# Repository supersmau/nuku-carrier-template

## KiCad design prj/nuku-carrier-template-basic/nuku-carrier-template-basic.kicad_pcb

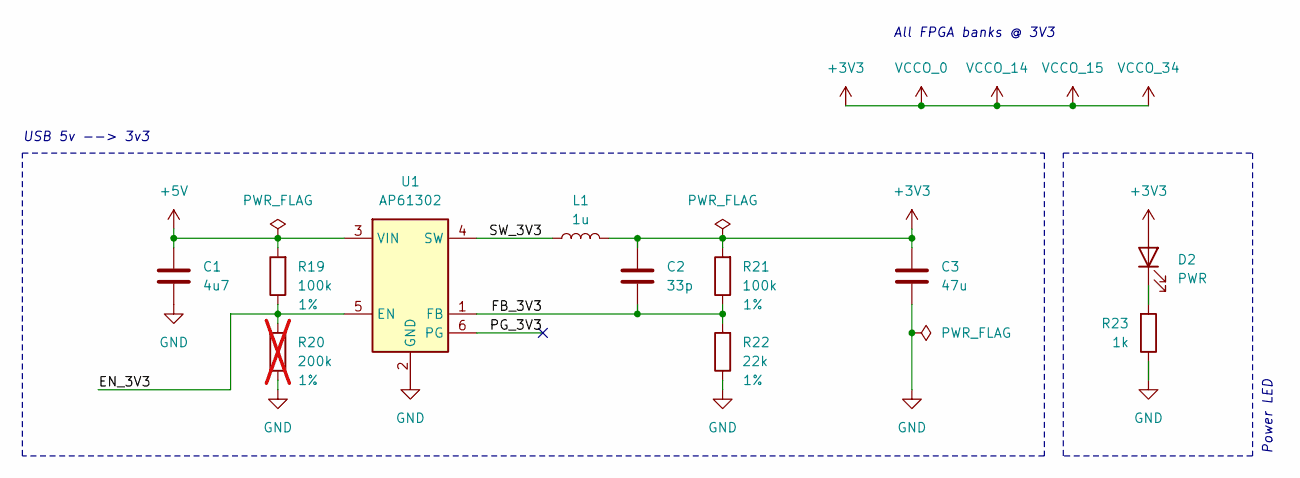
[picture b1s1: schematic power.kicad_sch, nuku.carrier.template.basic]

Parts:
C1: 4u7; C_0603_1608Metric; LCSC C19666
C2: 33p; C_0402_1005Metric; LCSC C1562
C3: 47u; C_0805_2012Metric; LCSC C16780
D2: PWR; LED_0805_2012Metric; LCSC C2297
L1: 1u; L_Changjiang_FNR252010S; Mfr. Part FTC252010S1R0MBCA; LCSC C5832356
R19, R21: 100k; R_0402_1005Metric; Tolerance 1%; LCSC C25741
R20: 200k; R_0402_1005Metric; Tolerance 1%; LCSC C25764; not fitted
R22: 22k; R_0402_1005Metric; Tolerance 1%; LCSC C25768
R23: 1k; R_0402_1005Metric; LCSC C11702
U1: AP61302; SOT-563; LCSC C3193204

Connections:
+3V3: C2.1, C3.1, D2.2 (A), L1.2, R21.2; also elsewhere on the board
+5V: C1.1, R19.2, U1.3 (VIN); also elsewhere on the board
/power/EN_3V3: R19.1, R20.2, U1.5 (EN)
/power/FB_3V3: C2.2, R21.1, R22.2, U1.1 (FB)
/power/PG_3V3: U1.6 (PG)
/power/SW_3V3: L1.1, U1.4 (SW)
GND: C1.2, C3.2, R20.1, R22.1, R23.1, U1.2 (GND); also elsewhere on the board
unnamed: D2.1 (K), R23.2

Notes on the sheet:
All FPGA banks @ 3V3
USB 5v --> 3v3
Power LED

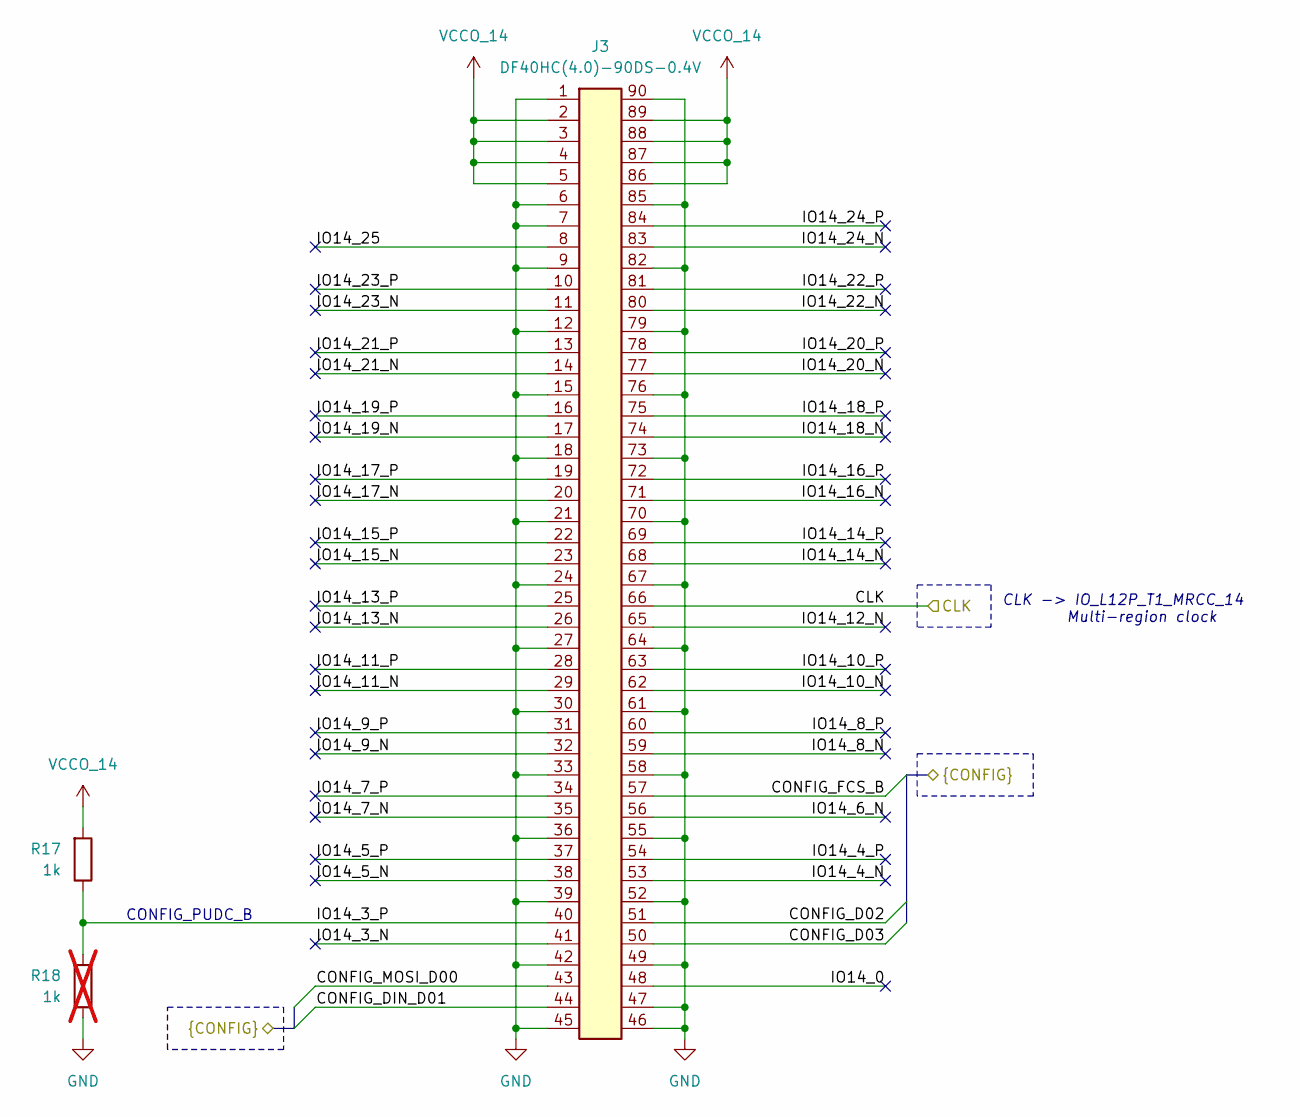
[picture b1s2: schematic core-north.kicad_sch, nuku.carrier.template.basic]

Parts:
J3: DF40HC(4.0)-90DS-0.4V; DF40C-90DS-0.4V; LCSC C2911197
R17: 1k; R_0402_1005Metric; LCSC C11702
R18: 1k; R_0402_1005Metric; LCSC C11702; not fitted

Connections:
+3V3: J3.2, J3.3, J3.4, J3.5, J3.86, J3.87, J3.88, J3.89, R17.2; also elsewhere on the board
/config/CLK: J3.66; also elsewhere on the board
/config/CONFIG_D02: J3.51; also elsewhere on the board
/config/CONFIG_D03: J3.50; also elsewhere on the board
/config/CONFIG_DIN_D01: J3.44; also elsewhere on the board
/config/CONFIG_FCS_B: J3.57; also elsewhere on the board
/config/CONFIG_MOSI_D00: J3.43; also elsewhere on the board
/core-north-14/IO14_0: J3.48
/core-north-14/IO14_3_N: J3.41
/core-north-14/IO14_3_P: J3.40, R17.1, R18.2
/core-north-14/IO14_4_N: J3.53
/core-north-14/IO14_4_P: J3.54
/core-north-14/IO14_5_N: J3.38
/core-north-14/IO14_5_P: J3.37
/core-north-14/IO14_6_N: J3.56
/core-north-14/IO14_7_N: J3.35
/core-north-14/IO14_7_P: J3.34
/core-north-14/IO14_8_N: J3.59
/core-north-14/IO14_8_P: J3.60
/core-north-14/IO14_9_N: J3.32
/core-north-14/IO14_9_P: J3.31
/core-north-14/IO14_10_N: J3.62
/core-north-14/IO14_10_P: J3.63
/core-north-14/IO14_11_N: J3.29
/core-north-14/IO14_11_P: J3.28
/core-north-14/IO14_12_N: J3.65
/core-north-14/IO14_13_N: J3.26
/core-north-14/IO14_13_P: J3.25
/core-north-14/IO14_14_N: J3.68
/core-north-14/IO14_14_P: J3.69
/core-north-14/IO14_15_N: J3.23
/core-north-14/IO14_15_P: J3.22
/core-north-14/IO14_16_N: J3.71
/core-north-14/IO14_16_P: J3.72
/core-north-14/IO14_17_N: J3.20
/core-north-14/IO14_17_P: J3.19
/core-north-14/IO14_18_N: J3.74
/core-north-14/IO14_18_P: J3.75
/core-north-14/IO14_19_N: J3.17
/core-north-14/IO14_19_P: J3.16
/core-north-14/IO14_20_N: J3.77
/core-north-14/IO14_20_P: J3.78
/core-north-14/IO14_21_N: J3.14
/core-north-14/IO14_21_P: J3.13
/core-north-14/IO14_22_N: J3.80
/core-north-14/IO14_22_P: J3.81
/core-north-14/IO14_23_N: J3.11
/core-north-14/IO14_23_P: J3.10
/core-north-14/IO14_24_N: J3.83
/core-north-14/IO14_24_P: J3.84
/core-north-14/IO14_25: J3.8
GND: J3.1, J3.6, J3.7, J3.9, J3.12, J3.15, J3.18, J3.21, J3.24, J3.27, J3.30, J3.33, J3.36, J3.39, J3.42, J3.45, J3.46, J3.47, J3.49, J3.52, J3.55, J3.58, J3.61, J3.64, J3.67, J3.70, J3.73, J3.76, J3.79, J3.82, J3.85, J3.90, R18.1; also elsewhere on the board

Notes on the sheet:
CONFIG_PUDC_B
CLK -> IO_L12P_T1_MRCC_14 Multi-region clock

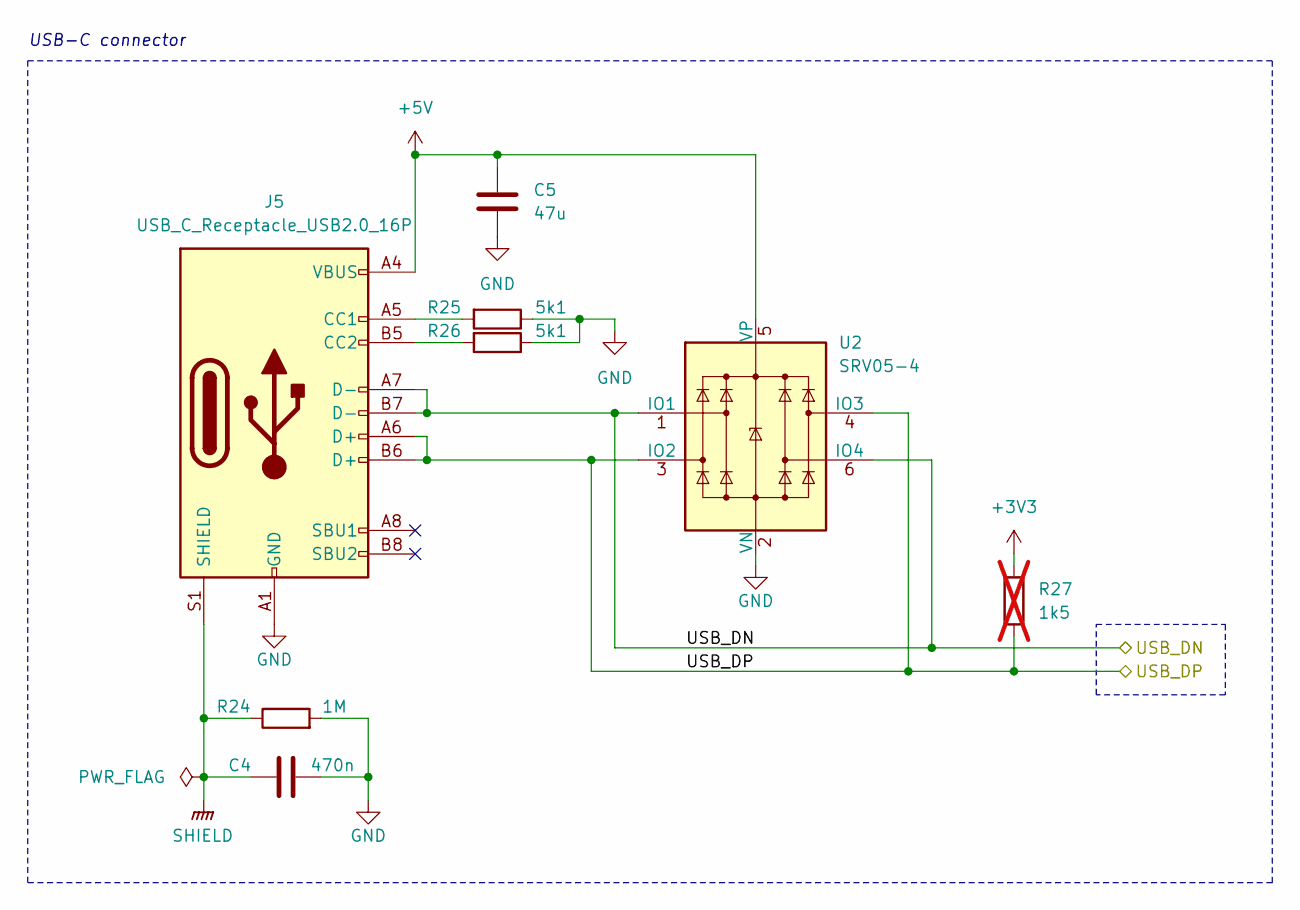
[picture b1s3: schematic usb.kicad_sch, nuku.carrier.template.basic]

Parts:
C4: 470n; C_0402_1005Metric; LCSC C47339
C5: 47u; C_0805_2012Metric; LCSC C16780
J5: USB_C_Receptacle_USB2.0_16P; TYPE-C16PIN; LCSC C393939
R24: 1M; R_0402_1005Metric; LCSC C26083
R25, R26: 5k1; R_0402_1005Metric; LCSC C25905
R27: 1k5; R_0402_1005Metric; LCSC C25867; not fitted
U2: SRV05-4; SOT-23-6; LCSC C7420376

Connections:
+5V: C5.1, J5.A4 (VBUS), J5.A9 (VBUS), J5.B4 (VBUS), J5.B9 (VBUS), U2.5 (VP); also elsewhere on the board
/bridge/USB_DN: J5.A7 (D-), J5.B7 (D-), U2.1 (IO1), U2.6 (IO4); also elsewhere on the board
/bridge/USB_DP: J5.A6 (D+), J5.B6 (D+), R27.1, U2.3 (IO2), U2.4 (IO3); also elsewhere on the board
GND: C4.1, C5.2, J5.A1 (GND), J5.A12 (GND), J5.B1 (GND), J5.B12 (GND), R24.2, R25.1, R26.1, U2.2 (VN); also elsewhere on the board
unnamed: J5.A5 (CC1), R25.2
unnamed: J5.B5 (CC2), R26.2
SHIELD: C4.2, J5.S1 (SHIELD), R24.1

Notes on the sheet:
USB-C connector

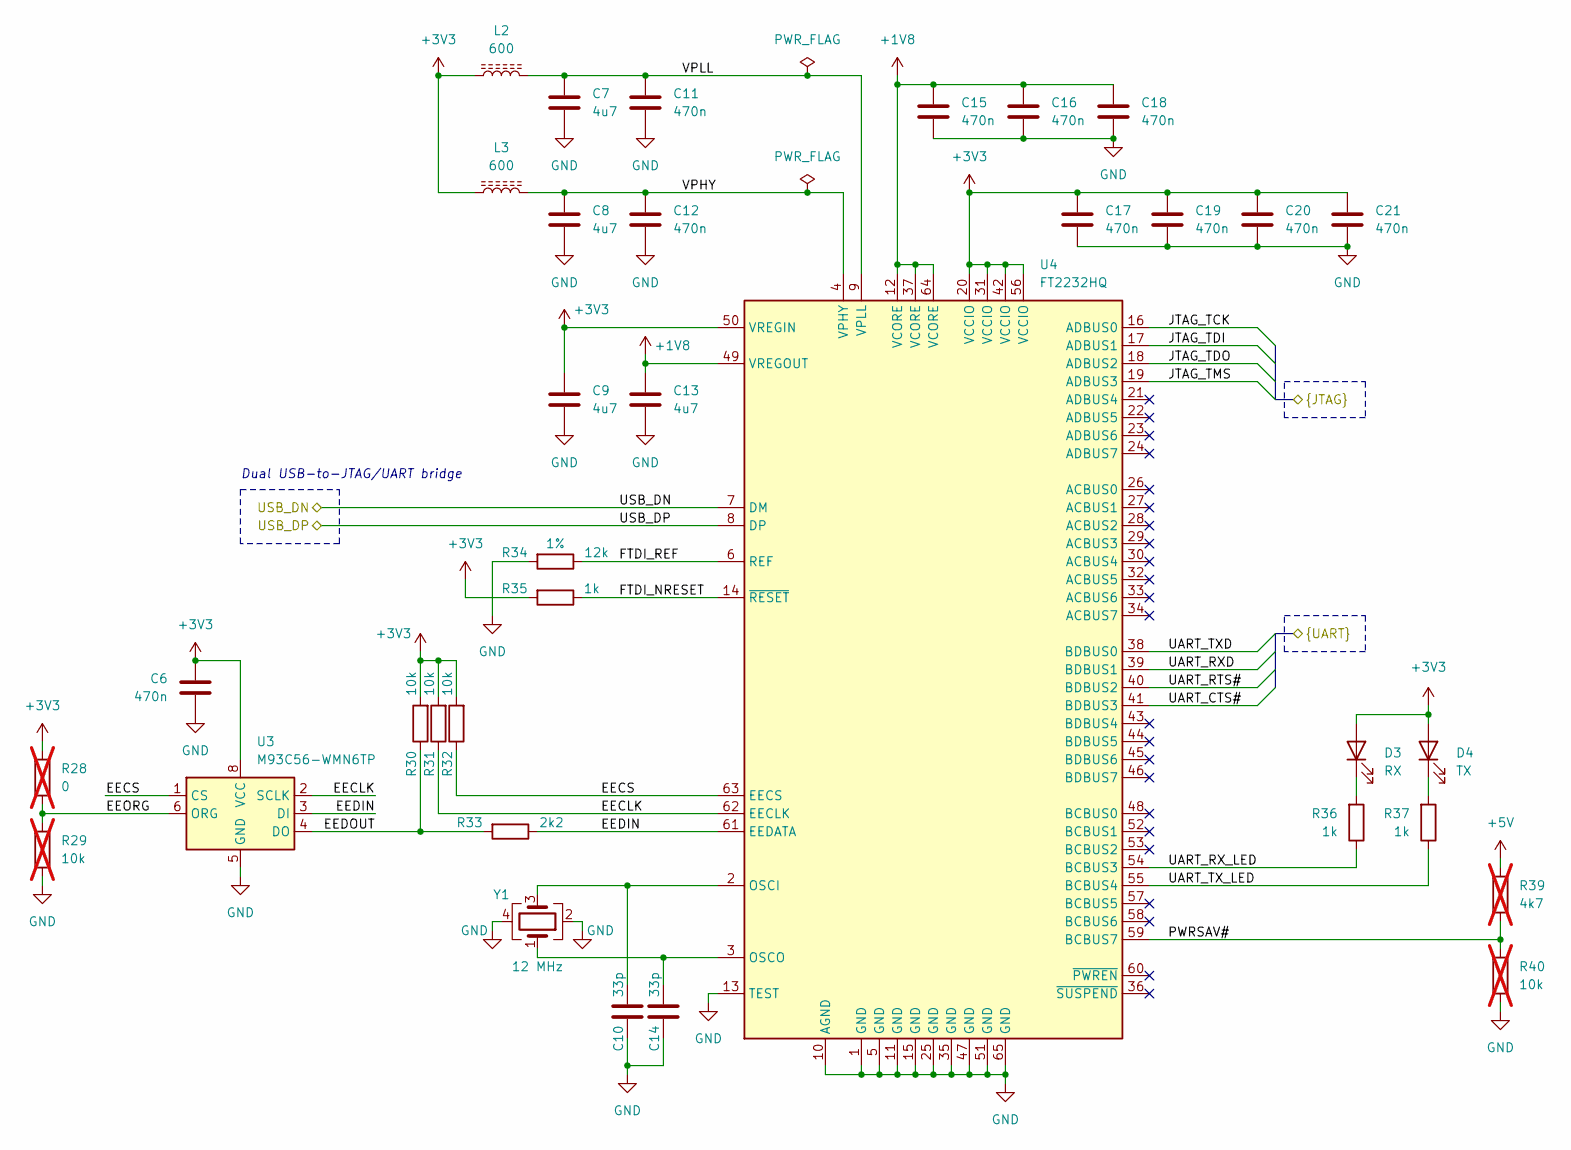
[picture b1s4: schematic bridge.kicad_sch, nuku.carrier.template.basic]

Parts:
C6, C11, C12, C15, C16, C17, C18, C19, C20, C21: 470n; C_0402_1005Metric; LCSC C47339
C7, C8, C9, C13: 4u7; C_0603_1608Metric; LCSC C19666
C10, C14: 33p; C_0402_1005Metric; LCSC C1562
D3: RX; LED_0805_2012Metric; LCSC C2297
D4: TX; LED_0805_2012Metric; LCSC C2297
L2, L3: 600; L_0603_1608Metric; LCSC C1002
R28: 0; R_0402_1005Metric; LCSC C17168; not fitted
R29, R40: 10k; R_0402_1005Metric; LCSC C25744; not fitted
R30, R31, R32: 10k; R_0402_1005Metric; LCSC C25744
R33: 2k2; R_0402_1005Metric; LCSC C25879
R34: 12k; R_0402_1005Metric; Tolerance 1%; LCSC C25752
R35, R36, R37: 1k; R_0402_1005Metric; LCSC C11702
R39: 4k7; R_0402_1005Metric; LCSC C25900; not fitted
U3: M93C56-WMN6TP; SOIC-8_3.9x4.9mm_P1.27mm; LCSC C283453
U4: FT2232HQ; QFN-64-1EP_9x9mm_P0.5mm_EP4.35x4.35mm; LCSC C193662
Y1: 12 MHz; Crystal_SMD_3225-4Pin_3.2x2.5mm; Part X322512MSB4SI; LCSC C9002

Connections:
+1V8: C13.1, C15.1, C16.1, C18.1, U4.12 (VCORE), U4.37 (VCORE), U4.49 (VREGOUT), U4.64 (VCORE)
+3V3: C6.1, C9.1, C17.1, C19.1, C20.1, C21.1, D3.2 (A), D4.2 (A), L2.1, L3.1, R28.2, R30.2, R31.2, R32.2, R35.2, U3.8 (VCC), U4.20 (VCCIO), U4.31 (VCCIO), U4.42 (VCCIO), U4.50 (VREGIN), U4.56 (VCCIO); also elsewhere on the board
/bridge/EECLK: R31.1, U3.2 (SCLK), U4.62 (EECLK)
/bridge/EECS: R32.1, U3.1 (CS), U4.63 (EECS)
/bridge/EEDIN: R33.1, U3.3 (DI), U4.61 (EEDATA)
/bridge/EEDOUT: R30.1, R33.2, U3.4 (DO)
/bridge/EEORG: R28.1, R29.2, U3.6 (ORG)
/bridge/FTDI_NRESET: R35.1, U4.14 (~RESET)
/bridge/FTDI_REF: R34.1, U4.6 (REF)
/bridge/JTAG_TCK: U4.16 (ADBUS0); also elsewhere on the board
/bridge/JTAG_TDI: U4.17 (ADBUS1); also elsewhere on the board
/bridge/JTAG_TDO: U4.18 (ADBUS2); also elsewhere on the board
/bridge/JTAG_TMS: U4.19 (ADBUS3); also elsewhere on the board
/bridge/PWRSAV#: R39.2, R40.2, U4.59 (BCBUS7)
/bridge/UART_CTS#: U4.41 (BDBUS3); also elsewhere on the board
/bridge/UART_RTS#: U4.40 (BDBUS2); also elsewhere on the board
/bridge/UART_RXD: U4.39 (BDBUS1); also elsewhere on the board
/bridge/UART_RX_LED: R36.1, U4.54 (BCBUS3)
/bridge/UART_TXD: U4.38 (BDBUS0); also elsewhere on the board
/bridge/UART_TX_LED: R37.1, U4.55 (BCBUS4)
/bridge/USB_DN: U4.7 (DM); also elsewhere on the board
/bridge/USB_DP: U4.8 (DP); also elsewhere on the board
/bridge/VPHY: C8.1, C12.1, L3.2, U4.4 (VPHY)
/bridge/VPLL: C7.1, C11.1, L2.2, U4.9 (VPLL)
GND: C6.2, C7.2, C8.2, C9.2, C10.1, C11.2, C12.2, C13.2, C14.1, C15.2, C16.2, C17.2, C18.2, C19.2, C20.2, C21.2, R29.1, R34.2, R40.1, U3.5 (GND), U4.1 (GND), U4.5 (GND), U4.10 (AGND), U4.11 (GND), U4.13 (TEST), U4.15 (GND), U4.25 (GND), U4.35 (GND), U4.47 (GND), U4.51 (GND), U4.65 (GND), Y1.2, Y1.4; also elsewhere on the board
unnamed: D3.1 (K), R36.2
unnamed: D4.1 (K), R37.2
unnamed: C10.2, U4.2 (OSCI), Y1.3
unnamed: C14.2, U4.3 (OSCO), Y1.1

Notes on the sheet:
Dual USB-to-JTAG/UART bridge

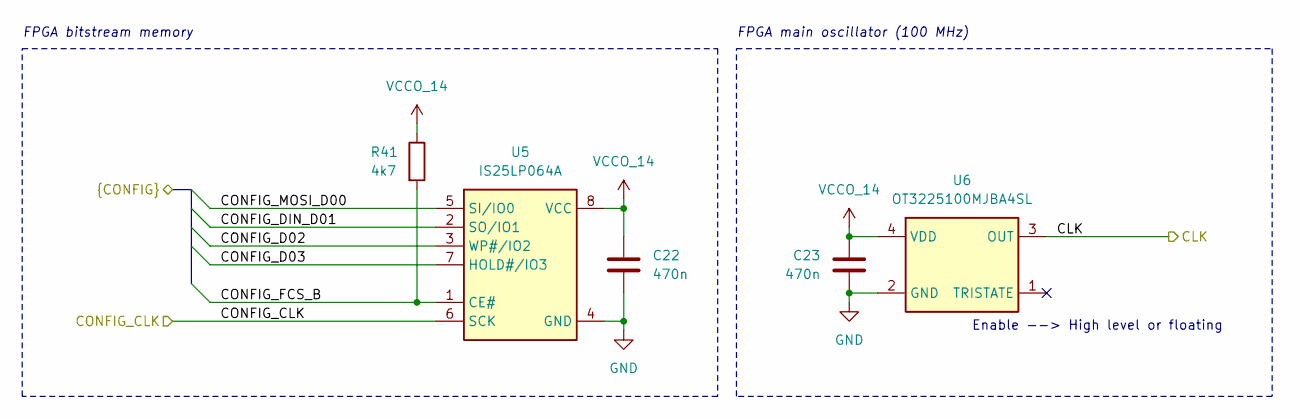
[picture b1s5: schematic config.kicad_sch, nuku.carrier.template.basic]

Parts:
C22, C23: 470n; C_0402_1005Metric; LCSC C47339
R41: 4k7; R_0402_1005Metric; LCSC C25900
U5: IS25LP064A; SOIC-8_5.3x5.3mm_P1.27mm; LCSC C2841348
U6: OT3225100MJBA4SL; Crystal_SMD_3225-4Pin_3.2x2.5mm; LCSC C4353707

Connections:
+3V3: C22.1, C23.1, R41.1, U5.8 (VCC), U6.4 (VDD); also elsewhere on the board
/config/CLK: U6.3 (OUT); also elsewhere on the board
/config/CONFIG_CLK: U5.6 (SCK); also elsewhere on the board
/config/CONFIG_D02: U5.3 (WP#/IO2); also elsewhere on the board
/config/CONFIG_D03: U5.7 (HOLD#/IO3); also elsewhere on the board
/config/CONFIG_DIN_D01: U5.2 (SO/IO1); also elsewhere on the board
/config/CONFIG_FCS_B: R41.2, U5.1 (CE#); also elsewhere on the board
/config/CONFIG_MOSI_D00: U5.5 (SI/IO0); also elsewhere on the board
GND: C22.2, C23.2, U5.4 (GND), U6.2 (GND); also elsewhere on the board

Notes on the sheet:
Enable --> High level or floating
FPGA main oscillator (100 MHz)
FPGA bitstream memory

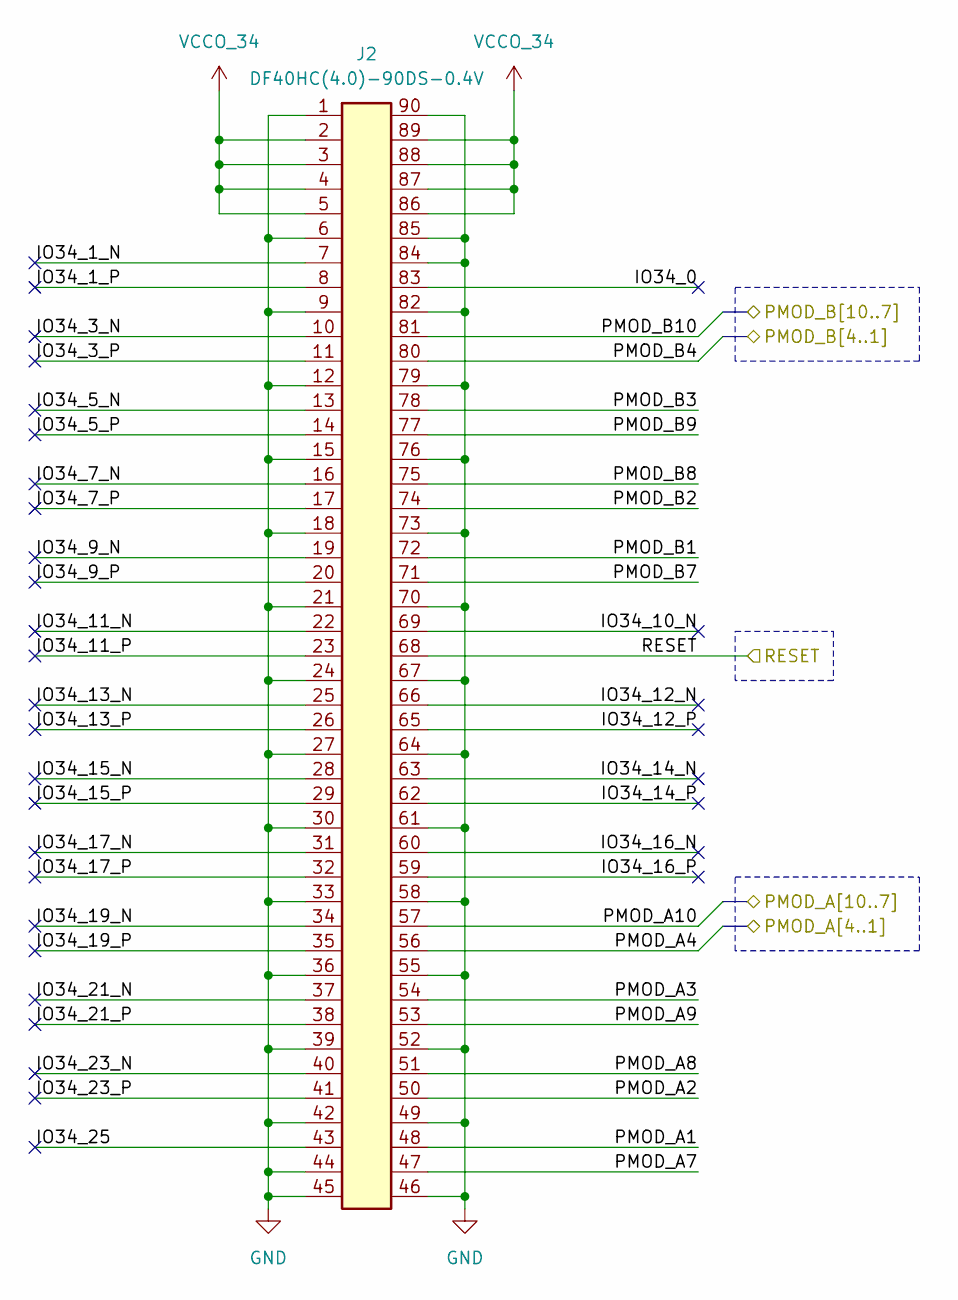
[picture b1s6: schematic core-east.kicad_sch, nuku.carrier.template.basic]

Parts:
J2: DF40HC(4.0)-90DS-0.4V; DF40C-90DS-0.4V; LCSC C2911197

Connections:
+3V3: J2.2, J2.3, J2.4, J2.5, J2.86, J2.87, J2.88, J2.89; also elsewhere on the board
/core-east-34/IO34_0: J2.83
/core-east-34/IO34_1_N: J2.7
/core-east-34/IO34_1_P: J2.8
/core-east-34/IO34_3_N: J2.10
/core-east-34/IO34_3_P: J2.11
/core-east-34/IO34_5_N: J2.13
/core-east-34/IO34_5_P: J2.14
/core-east-34/IO34_7_N: J2.16
/core-east-34/IO34_7_P: J2.17
/core-east-34/IO34_9_N: J2.19
/core-east-34/IO34_9_P: J2.20
/core-east-34/IO34_10_N: J2.69
/core-east-34/IO34_11_N: J2.22
/core-east-34/IO34_11_P: J2.23
/core-east-34/IO34_12_N: J2.66
/core-east-34/IO34_12_P: J2.65
/core-east-34/IO34_13_N: J2.25
/core-east-34/IO34_13_P: J2.26
/core-east-34/IO34_14_N: J2.63
/core-east-34/IO34_14_P: J2.62
/core-east-34/IO34_15_N: J2.28
/core-east-34/IO34_15_P: J2.29
/core-east-34/IO34_16_N: J2.60
/core-east-34/IO34_16_P: J2.59
/core-east-34/IO34_17_N: J2.31
/core-east-34/IO34_17_P: J2.32
/core-east-34/IO34_19_N: J2.34
/core-east-34/IO34_19_P: J2.35
/core-east-34/IO34_21_N: J2.37
/core-east-34/IO34_21_P: J2.38
/core-east-34/IO34_23_N: J2.40
/core-east-34/IO34_23_P: J2.41
/core-east-34/IO34_25: J2.43
/core-east-34/PMOD_A1: J2.48; also elsewhere on the board
/core-east-34/PMOD_A2: J2.50; also elsewhere on the board
/core-east-34/PMOD_A3: J2.54; also elsewhere on the board
/core-east-34/PMOD_A4: J2.56; also elsewhere on the board
/core-east-34/PMOD_A7: J2.47; also elsewhere on the board
/core-east-34/PMOD_A8: J2.51; also elsewhere on the board
/core-east-34/PMOD_A9: J2.53; also elsewhere on the board
/core-east-34/PMOD_A10: J2.57; also elsewhere on the board
/core-east-34/PMOD_B1: J2.72; also elsewhere on the board
/core-east-34/PMOD_B2: J2.74; also elsewhere on the board
/core-east-34/PMOD_B3: J2.78; also elsewhere on the board
/core-east-34/PMOD_B4: J2.80; also elsewhere on the board
/core-east-34/PMOD_B7: J2.71; also elsewhere on the board
/core-east-34/PMOD_B8: J2.75; also elsewhere on the board
/core-east-34/PMOD_B9: J2.77; also elsewhere on the board
/core-east-34/PMOD_B10: J2.81; also elsewhere on the board
/core-east-34/RESET: J2.68; also elsewhere on the board
GND: J2.1, J2.6, J2.9, J2.12, J2.15, J2.18, J2.21, J2.24, J2.27, J2.30, J2.33, J2.36, J2.39, J2.42, J2.44, J2.45, J2.46, J2.49, J2.52, J2.55, J2.58, J2.61, J2.64, J2.67, J2.70, J2.73, J2.76, J2.79, J2.82, J2.84, J2.85, J2.90; also elsewhere on the board

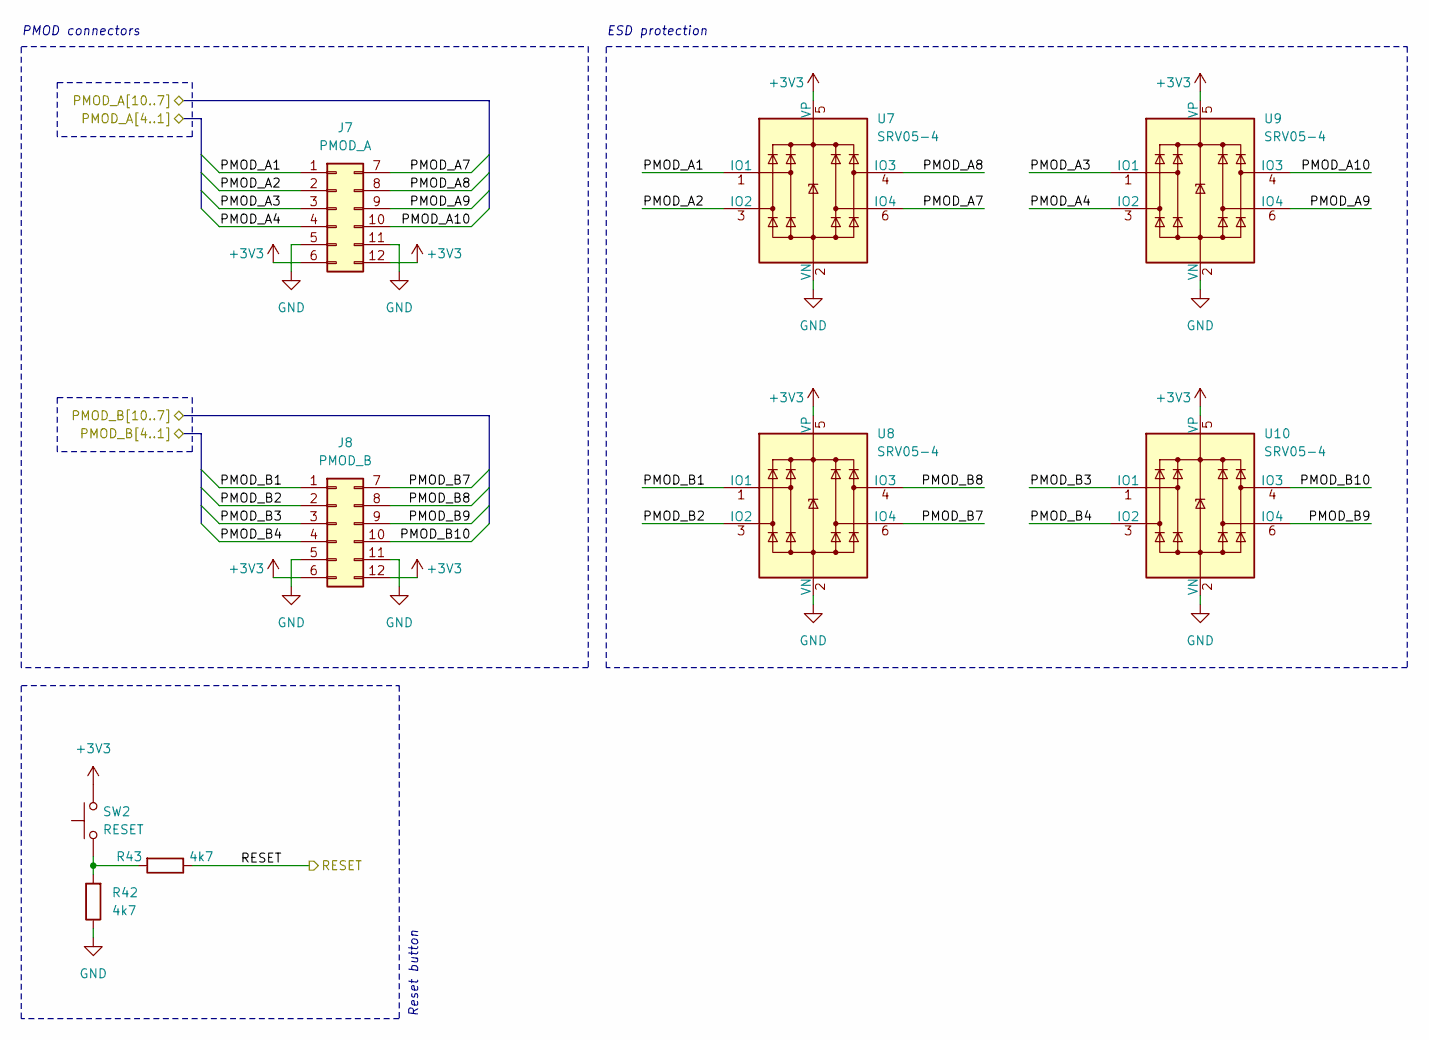
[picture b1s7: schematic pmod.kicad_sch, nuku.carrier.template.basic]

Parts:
J7: PMOD_A; PMOD_PinSocket_2x06_P2.54mm_Horizontal; LCSC C2936003
J8: PMOD_B; PMOD_PinSocket_2x06_P2.54mm_Horizontal; LCSC C2936003
R42, R43: 4k7; R_0402_1005Metric; LCSC C25900
SW2: RESET; TS-1088-AR02016; LCSC C720477
U7, U8, U9, U10: SRV05-4; SOT-23-6; LCSC C7420376

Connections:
+3V3: J7.6, J7.12, J8.6, J8.12, SW2.2, U7.5 (VP), U8.5 (VP), U9.5 (VP), U10.5 (VP); also elsewhere on the board
/core-east-34/PMOD_A1: J7.1, U7.1 (IO1); also elsewhere on the board
/core-east-34/PMOD_A2: J7.2, U7.3 (IO2); also elsewhere on the board
/core-east-34/PMOD_A3: J7.3, U9.1 (IO1); also elsewhere on the board
/core-east-34/PMOD_A4: J7.4, U9.3 (IO2); also elsewhere on the board
/core-east-34/PMOD_A7: J7.7, U7.6 (IO4); also elsewhere on the board
/core-east-34/PMOD_A8: J7.8, U7.4 (IO3); also elsewhere on the board
/core-east-34/PMOD_A9: J7.9, U9.6 (IO4); also elsewhere on the board
/core-east-34/PMOD_A10: J7.10, U9.4 (IO3); also elsewhere on the board
/core-east-34/PMOD_B1: J8.1, U8.1 (IO1); also elsewhere on the board
/core-east-34/PMOD_B2: J8.2, U8.3 (IO2); also elsewhere on the board
/core-east-34/PMOD_B3: J8.3, U10.1 (IO1); also elsewhere on the board
/core-east-34/PMOD_B4: J8.4, U10.3 (IO2); also elsewhere on the board
/core-east-34/PMOD_B7: J8.7, U8.6 (IO4); also elsewhere on the board
/core-east-34/PMOD_B8: J8.8, U8.4 (IO3); also elsewhere on the board
/core-east-34/PMOD_B9: J8.9, U10.6 (IO4); also elsewhere on the board
/core-east-34/PMOD_B10: J8.10, U10.4 (IO3); also elsewhere on the board
/core-east-34/RESET: R43.1; also elsewhere on the board
GND: J7.5, J7.11, J8.5, J8.11, R42.1, U7.2 (VN), U8.2 (VN), U9.2 (VN), U10.2 (VN); also elsewhere on the board
unnamed: R42.2, R43.2, SW2.1

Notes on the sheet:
ESD protection
Reset button
PMOD connectors

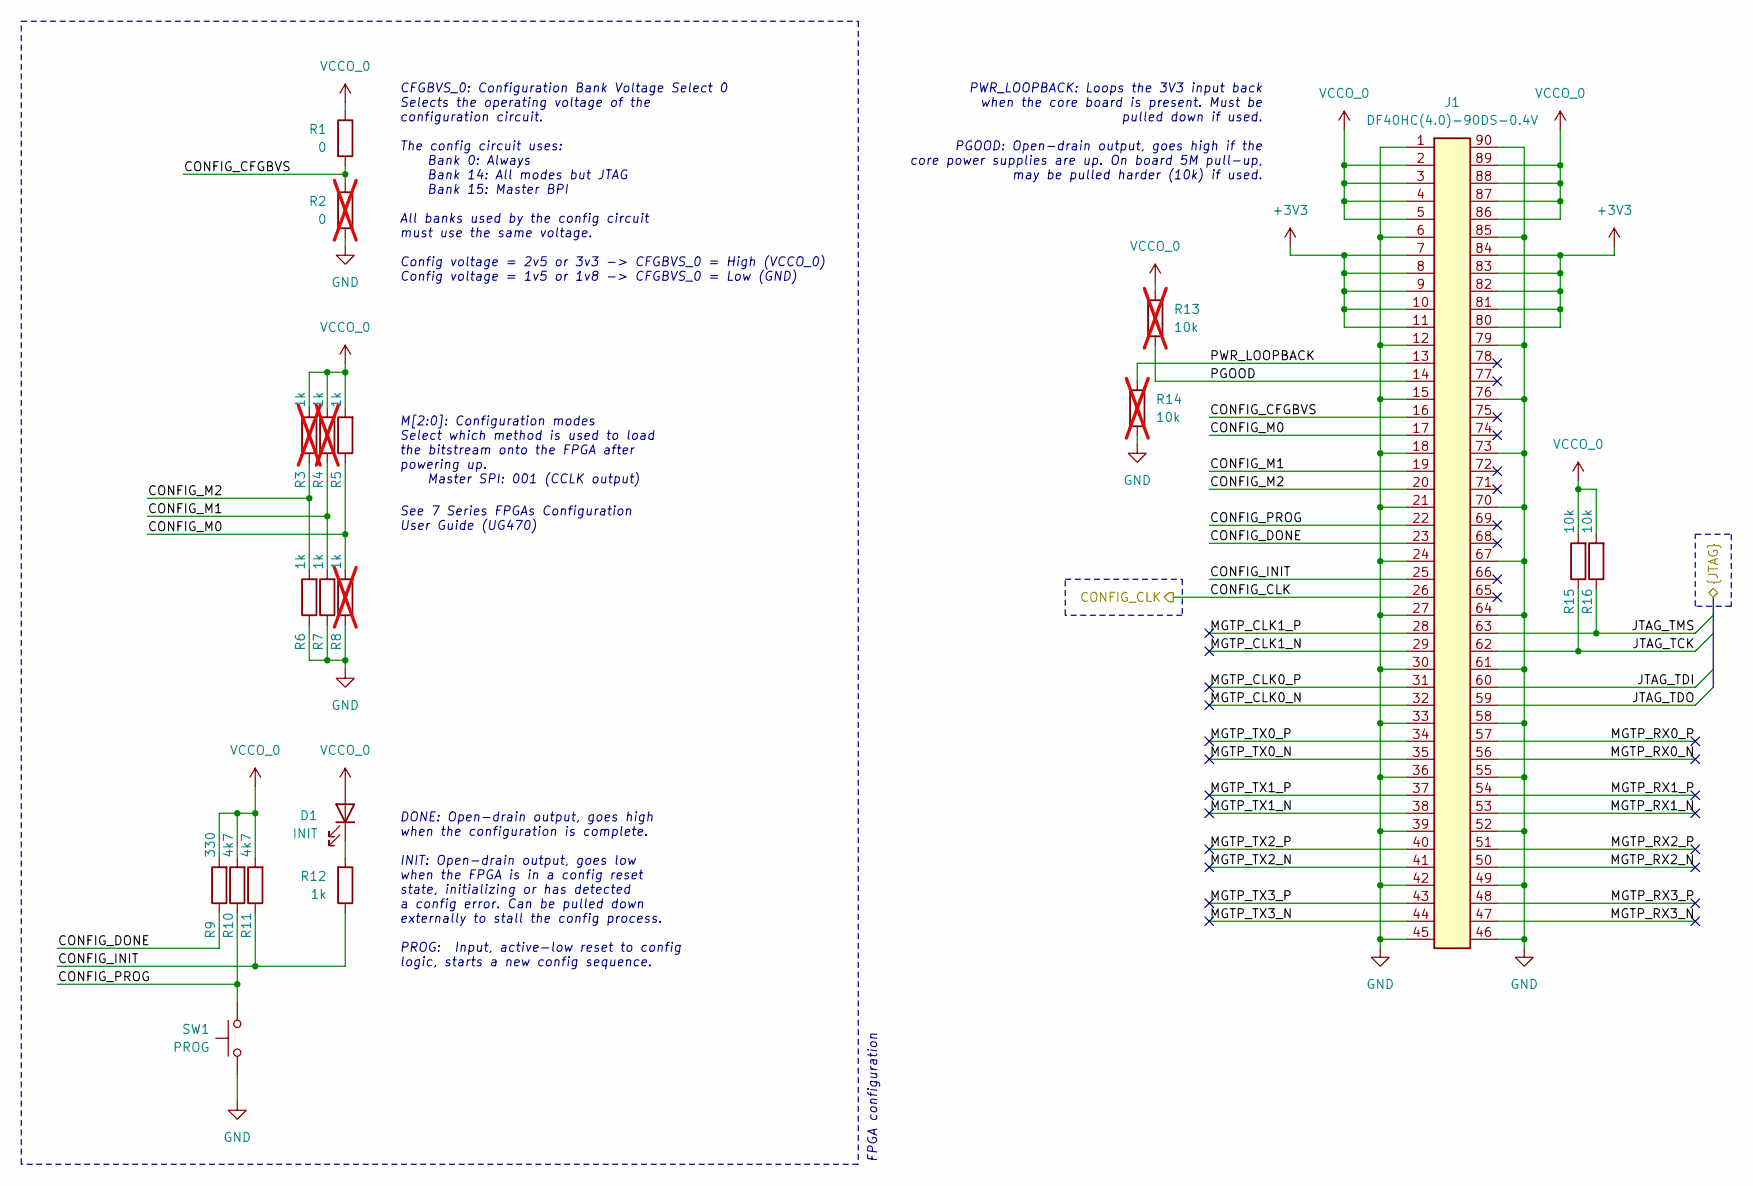
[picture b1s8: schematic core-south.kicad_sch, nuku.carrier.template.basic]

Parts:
D1: INIT; LED_0805_2012Metric; LCSC C2297
J1: DF40HC(4.0)-90DS-0.4V; DF40C-90DS-0.4V; LCSC C2911197
R1: 0; R_0402_1005Metric; LCSC C17168
R2: 0; R_0402_1005Metric; LCSC C17168; not fitted
R3, R4, R8: 1k; R_0402_1005Metric; LCSC C11702; not fitted
R5, R6, R7, R12: 1k; R_0402_1005Metric; LCSC C11702
R9: 330; R_0402_1005Metric; LCSC C25104
R10, R11: 4k7; R_0402_1005Metric; LCSC C25900
R13, R14: 10k; R_0402_1005Metric; LCSC C25744; not fitted
R15, R16: 10k; R_0402_1005Metric; LCSC C25744
SW1: PROG; TS-1088-AR02016; LCSC C720477

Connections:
+3V3: D1.2 (A), J1.2, J1.3, J1.4, J1.5, J1.7, J1.8, J1.9, J1.10, J1.11, J1.80, J1.81, J1.82, J1.83, J1.84, J1.86, J1.87, J1.88, J1.89, R1.1, R3.2, R4.2, R5.2, R9.2, R10.2, R11.2, R13.2, R15.2, R16.2; also elsewhere on the board
/bridge/JTAG_TCK: J1.62, R15.1; also elsewhere on the board
/bridge/JTAG_TDI: J1.60; also elsewhere on the board
/bridge/JTAG_TDO: J1.59; also elsewhere on the board
/bridge/JTAG_TMS: J1.63, R16.1; also elsewhere on the board
/config/CONFIG_CLK: J1.26; also elsewhere on the board
/core-south-0/CONFIG_CFGBVS: J1.16, R1.2, R2.1
/core-south-0/CONFIG_DONE: J1.23, R9.1
/core-south-0/CONFIG_INIT: J1.25, R11.1, R12.1
/core-south-0/CONFIG_M0: J1.17, R5.1, R8.2
/core-south-0/CONFIG_M1: J1.19, R4.1, R7.2
/core-south-0/CONFIG_M2: J1.20, R3.1, R6.2
/core-south-0/CONFIG_PROG: J1.22, R10.1, SW1.2
/core-south-0/MGTP_CLK0_N: J1.32
/core-south-0/MGTP_CLK0_P: J1.31
/core-south-0/MGTP_CLK1_N: J1.29
/core-south-0/MGTP_CLK1_P: J1.28
/core-south-0/MGTP_RX0_N: J1.56
/core-south-0/MGTP_RX0_P: J1.57
/core-south-0/MGTP_RX1_N: J1.53
/core-south-0/MGTP_RX1_P: J1.54
/core-south-0/MGTP_RX2_N: J1.50
/core-south-0/MGTP_RX2_P: J1.51
/core-south-0/MGTP_RX3_N: J1.47
/core-south-0/MGTP_RX3_P: J1.48
/core-south-0/MGTP_TX0_N: J1.35
/core-south-0/MGTP_TX0_P: J1.34
/core-south-0/MGTP_TX1_N: J1.38
/core-south-0/MGTP_TX1_P: J1.37
/core-south-0/MGTP_TX2_N: J1.41
/core-south-0/MGTP_TX2_P: J1.40
/core-south-0/MGTP_TX3_N: J1.44
/core-south-0/MGTP_TX3_P: J1.43
/core-south-0/PGOOD: J1.14, R13.1
/core-south-0/PWR_LOOPBACK: J1.13, R14.2
GND: J1.1, J1.6, J1.12, J1.15, J1.18, J1.21, J1.24, J1.27, J1.30, J1.33, J1.36, J1.39, J1.42, J1.45, J1.46, J1.49, J1.52, J1.55, J1.58, J1.61, J1.64, J1.67, J1.70, J1.73, J1.76, J1.79, J1.85, J1.90, R2.2, R6.1, R7.1, R8.1, R14.1, SW1.1; also elsewhere on the board
unnamed: D1.1 (K), R12.2

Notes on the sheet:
M[2:0]: Configuration modes Select which method is used to load the bitstream onto the FPGA after powering up. Master SPI: 001 (CCLK output)
FPGA configuration
See 7 Series FPGAs Configuration User Guide (UG470)
DONE: Open-drain output, goes high when the configuration is complete. INIT: Open-drain output, goes low when the FPGA is in a config reset state, initializing or has detected a config error. Can be pulled down externally to stall the config process. PROG: Input, active-low reset to config logic, s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
CFGBVS_0: Configuration Bank Voltage Select 0 Selects the operating voltage of the configuration circuit. The config circuit uses: Bank 0: Always Bank 14: All modes but JTAG Bank 15: Master BPI All banks used by the config circuit must use the same voltage. Config voltage = 2v5 or 3v3 -> CFGBVS_0 =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
PWR_LOOPBACK: Loops the 3V3 input back when the core board is present. Must be pulled down if used. PGOOD: Open-drain output, goes high if the core power supplies are up. On board 5M pull-up, may be pulled harder (10k) if used.

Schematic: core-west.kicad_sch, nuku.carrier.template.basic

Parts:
J4: DF40HC(4.0)-90DS-0.4V; DF40C-90DS-0.4V; LCSC C2911197

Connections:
+3V3: J4.2, J4.3, J4.4, J4.5, J4.86, J4.87, J4.88, J4.89; also elsewhere on the board
/bridge/UART_CTS#: J4.66; also elsewhere on the board
/bridge/UART_RTS#: J4.65; also elsewhere on the board
/bridge/UART_RXD: J4.63; also elsewhere on the board
/bridge/UART_TXD: J4.62; also elsewhere on the board
/core-west-15/IO15_0: J4.48
/core-west-15/IO15_1_N: J4.44
/core-west-15/IO15_1_P: J4.43
/core-west-15/IO15_2_N: J4.50
/core-west-15/IO15_2_P: J4.51
/core-west-15/IO15_3_N: J4.41
/core-west-15/IO15_3_P: J4.40
/core-west-15/IO15_4_N: J4.53
/core-west-15/IO15_4_P: J4.54
/core-west-15/IO15_5_N: J4.38
/core-west-15/IO15_5_P: J4.37
/core-west-15/IO15_6_N: J4.56
/core-west-15/IO15_6_P: J4.57
/core-west-15/IO15_7_N: J4.35
/core-west-15/IO15_7_P: J4.34
/core-west-15/IO15_8_N: J4.59
/core-west-15/IO15_8_P: J4.60
/core-west-15/IO15_9_N: J4.32
/core-west-15/IO15_9_P: J4.31
/core-west-15/IO15_11_N: J4.29
/core-west-15/IO15_11_P: J4.28
/core-west-15/IO15_13_N: J4.26
/core-west-15/IO15_13_P: J4.25
/core-west-15/IO15_14_N: J4.68
/core-west-15/IO15_14_P: J4.69
/core-west-15/IO15_15_N: J4.23
/core-west-15/IO15_15_P: J4.22
/core-west-15/IO15_16_N: J4.71
/core-west-15/IO15_16_P: J4.72
/core-west-15/IO15_17_N: J4.20
/core-west-15/IO15_17_P: J4.19
/core-west-15/IO15_18_N: J4.74
/core-west-15/IO15_18_P: J4.75
/core-west-15/IO15_19_N: J4.17
/core-west-15/IO15_19_P: J4.16
/core-west-15/IO15_20_N: J4.77
/core-west-15/IO15_20_P: J4.78
/core-west-15/IO15_21_N: J4.14
/core-west-15/IO15_21_P: J4.13
/core-west-15/IO15_22_N: J4.80
/core-west-15/IO15_22_P: J4.81
/core-west-15/IO15_23_N: J4.11
/core-west-15/IO15_23_P: J4.10
/core-west-15/IO15_24_N: J4.83
/core-west-15/IO15_24_P: J4.84
/core-west-15/IO15_25: J4.8
GND: J4.1, J4.6, J4.7, J4.9, J4.12, J4.15, J4.18, J4.21, J4.24, J4.27, J4.30, J4.33, J4.36, J4.39, J4.42, J4.45, J4.46, J4.47, J4.49, J4.52, J4.55, J4.58, J4.61, J4.64, J4.67, J4.70, J4.73, J4.76, J4.79, J4.82, J4.85, J4.90; also elsewhere on the board
